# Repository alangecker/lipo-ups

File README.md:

# LiPo UPS
a modular UPS utilizing any 2s LiPo Battery (e.g. for RC cars) 

**Status: draft! was not build & tested yet!**

## Features
- 50W output
- modular concept with off-the-shelf buck/boost converter modules for much flexibility
- read charging state via USB
- lots of battery protection features thanks to BQ24610
- "power path" design
- active balancing

## Specs
- Input: 9-12V and ≥5A

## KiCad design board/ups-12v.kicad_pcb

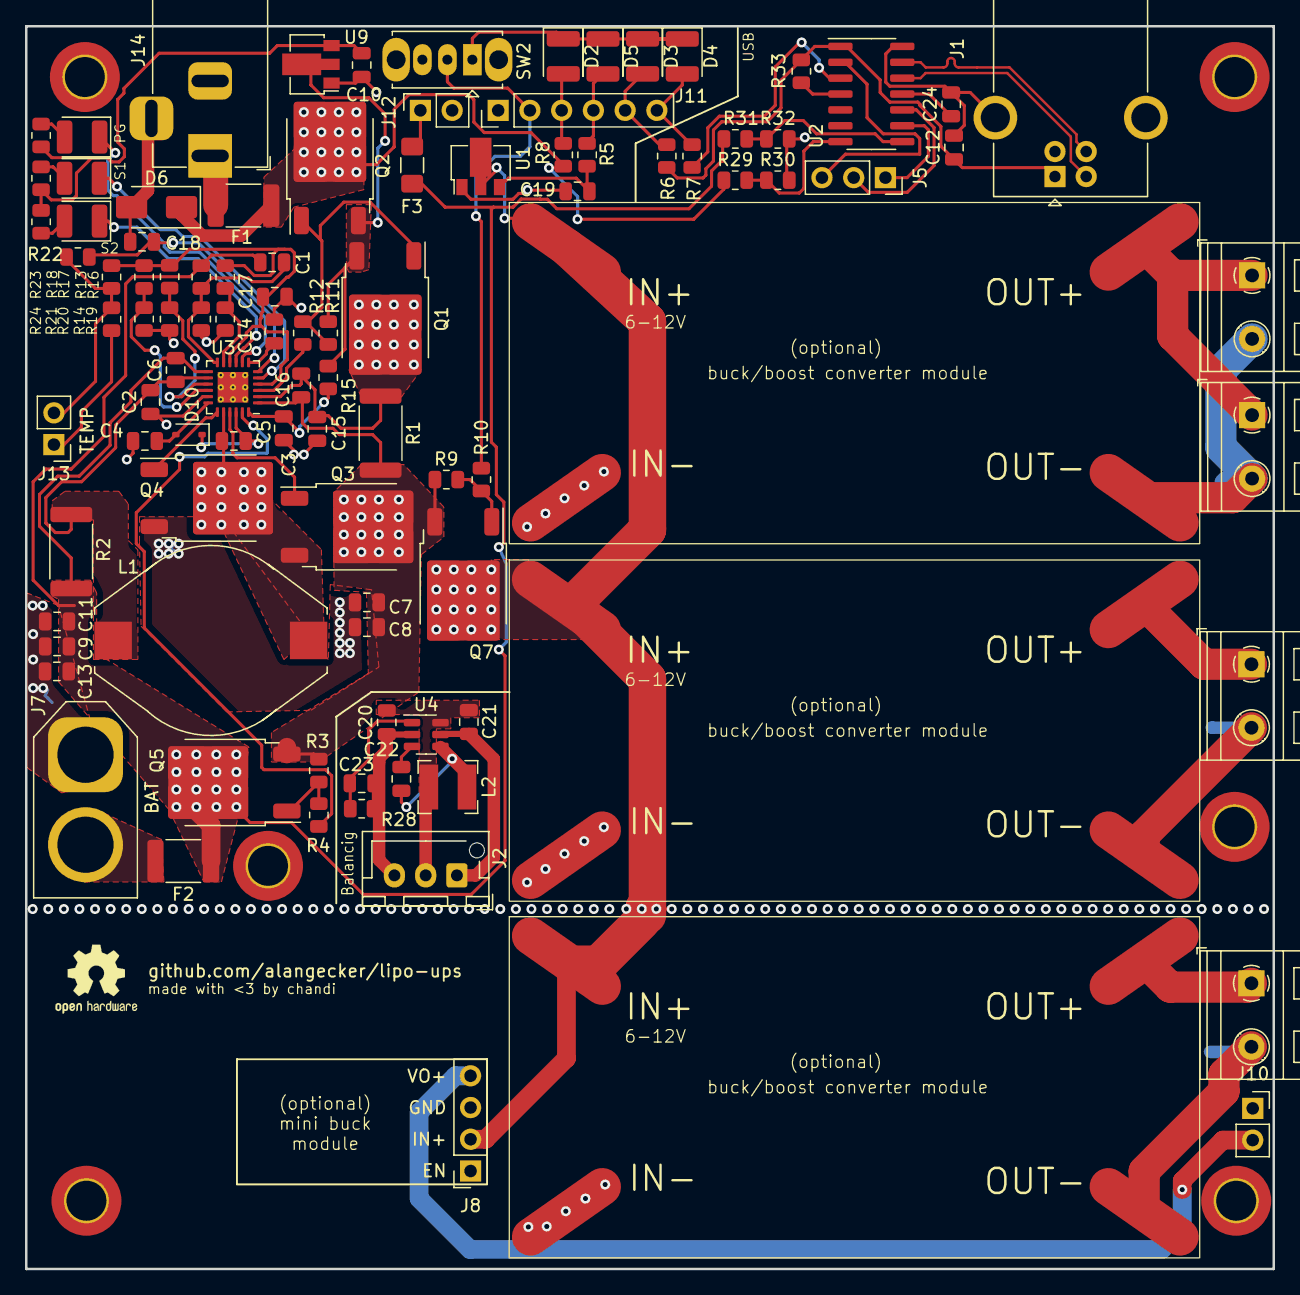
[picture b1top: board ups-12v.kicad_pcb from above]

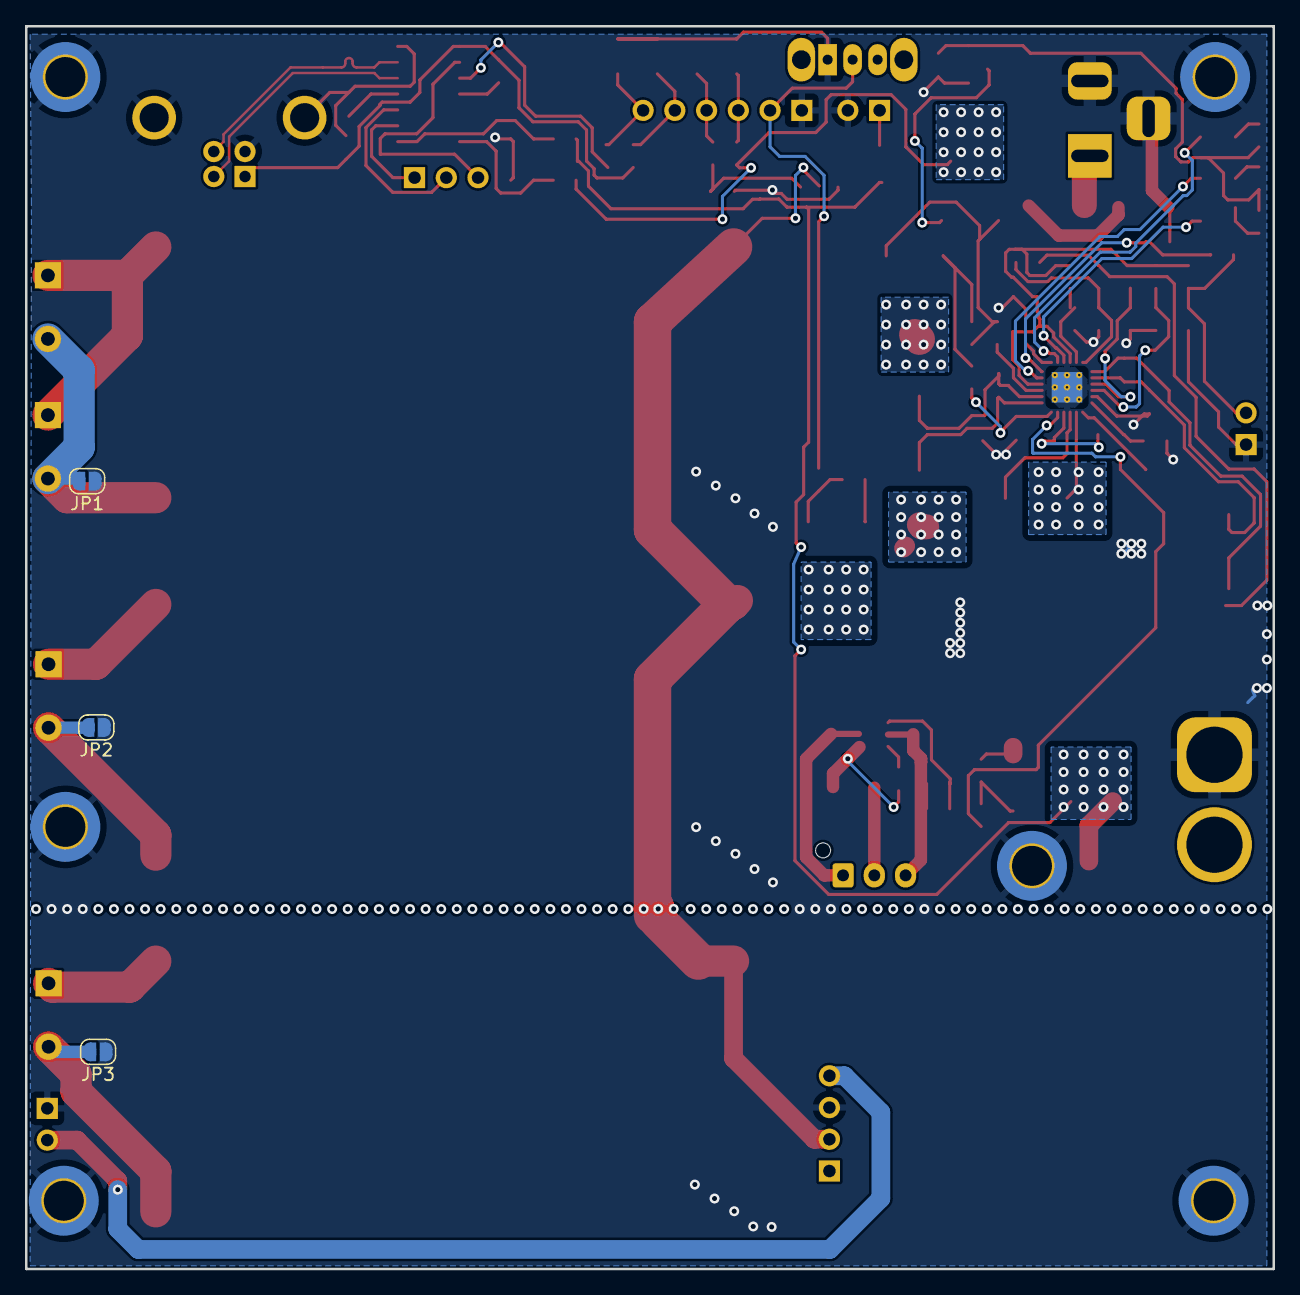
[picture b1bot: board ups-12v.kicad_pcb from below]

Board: 2 copper layers, 99.8 x 99.4 mm, 109 parts (3 on the bottom side), 67 nets.

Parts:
C1: 22pF; C_0805_2012Metric
C2, C5, C6, C12, C15, C16, C18: 0.1uF; C_0805_2012Metric
C3, C4, C17, C19, C24: 1uF; C_0805_2012Metric
C7, C8, C9, C11: 10u; C_0805_2012Metric
C10: 10uF; C_0805_2012Metric
C13: DNP; C_0805_2012Metric
C14: 56nF; C_0805_2012Metric
C20, C21: 2.2uF; C_0805_2012Metric
C22: 10nF; C_0805_2012Metric
C23: 1nF; C_0805_2012Metric
D2: CHG; LED_1210_3225Metric
D3: USB_ON; LED_1210_3225Metric
D4: SW; LED_1210_3225Metric
D5: PWR; LED_1210_3225Metric
D6: US1A; D_SMA
D7: S2; LED_1210_3225Metric
D8: S1; LED_1210_3225Metric
D9: PG; LED_1210_3225Metric
D10: 1N5819WS; D_SOD-323
F1, F2: 8A; Fuse_1812_4532Metric_Pad1.30x3.40mm_HandSolder
F3: 100mA; Fuse_1206_3216Metric_Pad1.42x1.75mm_HandSolder
H1, H2, H3, H4, H5, H6: MountingHole; MountingHole_3.2mm_M3_DIN965_Pad_TopBottom
J1: USB_B; USB_B_OST_USB-B1HSxx_Horizontal
J2: Balancig; JST_XH_B3B-XH-AM_1x03_P2.50mm_Vertical
J3, J4, J6, J9: TerminalBlock_RND_205-00232_1x02_P5.08mm_Horizontal
J5: Unused Pins; PinSocket_1x03_P2.54mm_Vertical
J7: BAT; AMASS_XT60-F_1x02_P7.20mm_Vertical
J8: Mini Buck Module; PinSocket_1x04_P2.54mm_Vertical
J10: PinSocket_1x02_P2.54mm_Vertical
J11: Front Panel; PinHeader_1x06_P2.54mm_Vertical
J12: Battery Meter; PinSocket_1x02_P2.54mm_Vertical
J13: TEMP; PinHeader_1x02_P2.54mm_Vertical
J14: V_in; BarrelJack_Horizontal
JP1, JP2, JP3: Jumper_2_Open; SolderJumper-2_P1.3mm_Open_RoundedPad1.0x1.5mm
L1: 6.8uH 6A; L_Fastron_PISR
L2: 1uH; L_Bourns-SRN4018
Q1, Q2, Q5, Q7: AOD423; TO-252-2
Q3, Q4: AOD484; TO-252-2
R1, R2: 10m; R_2512_6332Metric
R3, R9, R11, R17: 100k; R_0805_2012Metric
R4, R10, R12: 1k; R_0805_2012Metric
R5, R25, R26, R27: 47; R_0805_2012Metric
R6, R7: 150; R_0805_2012Metric
R8: 470; R_0805_2012Metric
R13: 680k; R_0805_2012Metric
R14: 240k; R_0805_2012Metric
R15: 10; R_0805_2012Metric
R16, R18: 68k; R_0805_2012Metric
R19, R21: 33k; R_0805_2012Metric
R20, R30, R32, R33: 10k; R_0805_2012Metric
R22: 100; R_0805_2012Metric
R23: 9.31k; R_0805_2012Metric
R24: 430k; R_0805_2012Metric
R28: 25k; R_0805_2012Metric
R29, R31: 150k; R_0805_2012Metric
SW2: SW_SPDT; SW_Slide_1P2T_CK_OS102011MS2Q
U1, U9: HT7533-1; SOT-89-3
U2: MCP2221AxSL; SOIC-14_3.9x8.7mm_P1.27mm
U3: BQ24610; VQFN-24-1EP_4x4mm_P0.5mm_EP2.45x2.45mm_ThermalVias
U4: ETA3000S2G; SOT-23-6
U5, U6, U7: multi-converter

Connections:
+3.3VA: C17.1, R16.1, R17.1, R18.1, R23.2, U3.4 (CE), U3.10 (VREF)
/BAT: C1.1, C6.2, C9.1, C11.1, C13.1, F2.1, F3.1, Q5.2 (D), R2.2, R13.1, R31.1, U3.13 (SRN)
/SW_ON: R7.1, U2.3 (GP1)
/USB/D+: J1.3 (D+), U2.13 (D+)
/USB/D-: J1.2 (D-), U2.12 (D-)
/VUSB: C12.1, J1.1 (VBUS), R6.1, R33.1, U2.1 (VDD)
/Vin: D6.1 (K), F1.2, Q2.2 (D), R8.1, R29.1
/balancing/BATC: C20.1, C21.2, J2.2, L2.2, U4.6 (BATC)
/balancing/BATN: C20.2, C23.1, J2.3, R28.2, U4.2 (BATN)
/balancing/BATP: C21.1, J2.1, U4.5 (BATP)
/charger/PG: D9.1 (K), U3.8 (~PG(Open-drain))
/charger/STAT1: D8.1 (K), U3.5 (STAT1(Open-drain))
/charger/STAT2: D7.1 (K), U3.9 (STAT2(Open-drain))
/charger/SYS: C7.1, C8.1, C16.2, Q3.2 (D), Q5.3 (S), Q7.3 (S), R1.2, R3.1, R9.1, U3.1 (ACN)
/charger/TEMP: J13.2, R22.1, R23.1, R24.2
GND: C2.1, C3.2, C4.2, C7.2, C8.2, C9.2, C10.2, C11.2, C12.2, C13.2, C14.1, C15.1, C17.2, C18.1, C19.1, C24.2, D2.1 (K), D3.1 (K), D4.1 (K), D5.1 (K), D6.2 (A), H1.1, H2.1, H3.1, H4.1, H5.1, H6.1, J1.4 (GND), J1.5 (Shield), J7.1, J8.3, J10.1, J11.1, J12.2, J13.1, J14.2, J14.3, JP1.1 (A), JP2.1 (A), JP3.1 (A), Q4.3 (S), R14.2, R19.2, R20.2, R21.2, R24.1, R30.2, R32.2, SW2.1 (A), U1.1 (GND), U2.14 (VSS), U3.17 (GND), U3.25 (Thermal_Pad), U5.2 (IN-), U6.2 (IN-), U7.2 (IN-), U9.1 (GND)
unnamed: D2.2 (A), J11.3, R8.2
unnamed: D3.2 (A), J11.5, R6.2
unnamed: D4.2 (A), J11.6, R7.2
unnamed: D5.2 (A), J11.4, R5.2
unnamed: D7.2 (A), R25.2
unnamed: D8.2 (A), R27.2
unnamed: D9.2 (A), R26.2
unnamed: C4.1, D10.2 (A), U3.18 (REGN)
unnamed: C5.2, D10.1 (K), U3.22 (BTST)
unnamed: F1.1, J14.1
unnamed: J3.1, U6.3 (OUT+)
unnamed: J3.2, JP2.2 (B), U6.4 (OUT-)
unnamed: J4.1, J6.1, U5.3 (OUT+)
unnamed: J4.2, J6.2, JP1.2 (B), U5.4 (OUT-)
unnamed: J5.1, U2.9 (SDA)
unnamed: J5.2, U2.10 (SCL)
unnamed: J5.3, U2.2 (GP0)
unnamed: F2.2, J7.2
unnamed: J8.2, Q7.2 (D), U1.2 (VIN), U5.1 (IN+), U6.1 (IN+), U7.1 (IN+)
unnamed: J9.1, U7.3 (OUT+)
unnamed: J9.2, JP3.2 (B), U7.4 (OUT-)
unnamed: J8.4, J10.2
unnamed: J11.2, R10.2, SW2.2 (B)
unnamed: F3.2, J12.1
unnamed: C15.2, C16.1, Q1.2 (D), R1.1, U3.2 (ACP)
unnamed: Q1.1 (G), Q2.1 (G), R11.2, R12.1
unnamed: Q3.1 (G), U3.21 (HIDRV)
unnamed: C5.1, L1.1, Q3.3 (S), Q4.2 (D), U3.20 (PH)
unnamed: Q4.1 (G), U3.19 (LODRV)
unnamed: Q5.1 (G), R3.2, R4.2
unnamed: Q7.1 (G), R9.2, R10.1
unnamed: C19.2, R5.1, U1.3 (VOUT)
unnamed: R29.2, R30.1, U2.7 (GP2)
unnamed: R31.2, R32.1, U2.8 (GP3)
unnamed: C24.1, U2.11 (VUSB)
unnamed: R33.2, U2.4 (~RST)
unnamed: R18.2, R21.1, U3.16 (ACSET)
unnamed: R16.2, R19.1, U3.11 (ISET1)
unnamed: R17.2, R20.1, U3.15 (ISET2)
unnamed: C2.2, C6.1, L1.2, R2.1, U3.14 (SRP)
unnamed: C18.2, R22.2, U3.6 (TS)
unnamed: C14.2, U3.7 (TTC)
unnamed: C3.1, R15.2, U3.24 (VCC)
unnamed: C1.2, R13.2, R14.1, U3.12 (VFB)
unnamed: R12.2, U3.3 (~ACDRV)
unnamed: R4.1, U3.23 (~BATDRV)
unnamed: C22.1, U4.3 (BIAS)
unnamed: C23.2, R28.1, U4.1 (ISET)
unnamed: C22.2, L2.1, U4.4 (SW)
unnamed: C10.1, R25.1, R26.1, R27.1, U9.3 (VOUT)
VCC: Q1.3 (S), Q2.3 (S), R11.1, R15.1, U9.2 (VIN)

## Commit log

2023-09-07 incorporate review feedback
